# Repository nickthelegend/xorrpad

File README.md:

# xorrpad · v1.0.0

**Every market. One desk. Fourteen keys.**

xorrpad is a physical trading pad for Solana, backed by an Electron desk and
interfaces for the XOR phone app. Spot, perpetuals and YES/NO outcome markets
share programmable keys, an agent, remembered risk rules and an acceptance gate.
The ESP32-S3 prototype has 14 keys, a microphone, an amp and a 2.8-inch TFT.
The protocol supports a size/leverage knob; the current board has no wired encoder.

The order of work is a working board demo, then waitlist and reservations, then
bulk manufacturing. v1 uses your own local model or provider account and keys;
a paid hosted LLM service is outside this release. Nothing is removed in v1:
the original desk remains at `/classic`, alongside the nine-page desk, legacy
HTTP/voice paths, tokenized-stock book and NYSE-hours warnings.

## Architecture

```text
 ESP32-S3 pad                         XOR phone app (external Expo project)
 14 keys · mic · amp · TFT            BLE pairing/relay · signals · accept/deny
 link manager: USB > BLE > Wi-Fi <--> wallet signing · push integration target
       | USB-CDC NDJSON / Wi-Fi HTTPS             | HTTPS / wallet handoff
       v                                          v
 XOR desk (Electron on the Mac mini; responsive authenticated web view)
 ├─ serial / BLE central / HTTP / WebSocket link server and key programmer
 ├─ agent: Ollama locally or over Tailscale, or a bring-your-own-key provider
 ├─ voice: Deepgram STT → gated proposal → Deepgram TTS to desk / pad amp
 ├─ aggregator: Jupiter spot · Meteora DLMM · Phoenix perps · Jupiter Perps
 │              pm-AMM outcome markets on devnet
 ├─ memory + permissions → manual / policy auto-accept → executor
 │                         phone wallet (default) | capped session wallet
 └─ pad mirror · trade · predict · chats · models/keys · permissions
    positions · backtest · link; confirmed signature / Explorer receipt

 Separate devnet keeper: recurring pm-AMM markets + exact-expiry Pyth resolution
 Standalone site: waitlist + terms-gated Solana Pay USDC reservation checkout
```

The phone app source is not in this repository. Its BLE relay, notifications and
acceptance UI are integration targets, not a verified shipped phone release.
Transport tests prove the host simulator path. Firmware is **compiled, not yet
flashed**; physical BLE, keys, display, mic and amp still need a board check.
See [TESTING.md](TESTING.md) for the current full run and exact blockers.

## Venues

| Route / adapter id | Network | Implemented capability | Execution limit |
| --- | --- | --- | --- |
| Jupiter spot / `solana` (`jupiter` in router) | Mainnet reads | Mint-pinned spot/xStocks quotes and unsigned swaps; Jupiter can route through Meteora, Orca, Raydium and Phoenix spot | Live liquidity/quote required; a catalog entry does not guarantee a route |
| Meteora DLMM / `meteora` | Mainnet reads | Direct USDC-pair discovery, quotes and unsigned swaps, compared with Jupiter | No direct pool is reported as unlisted |
| Phoenix perps / `phoenix` | Mainnet reads | Live market discovery, depth quotes, position reads, unsigned open and ReduceOnly close | Enabled, funded trader/subaccount required; no public perps devnet verified |
| Jupiter Perps / `jupperps` | Mainnet reads | SOL/ETH/BTC marks, indicative quotes, on-chain fee reads, unsigned API open/close builders | Funded owner required; quote excludes ongoing borrow costs and is not a fill guarantee |
| PREDICT pm-AMM / `pmamm` | Devnet only in this app | Live YES/NO quotes, unsigned create/swap/claim, positions, creator-filtered stats and resolution evidence | Needs devnet SOL and mUSDC for a trade; funded end-to-end cycle remains blocked |

Every venue adapter only reads or builds unsigned transactions. The shared
executor handles signing/submission after acceptance. Missing fees remain unknown,
never zero. Token identity is the exact mint (or catalog `symbol@mint`), not a
ticker match; historical xStock liquidity exclusions are retained. Perp `size`
is USD collateral and notional is size × leverage; spot sells use asset units,
spot buys use USDC, and prediction sizes use devnet mUSDC.
[Venue evidence and quote assumptions](docs/VENUES.md).

## Trade lifecycle

1. **Signal:** a pad key, strategy scan, chat or voice intent creates a proposal.
2. **Proposal:** the aggregator compares real quotes and fees across eligible venues.
3. **Gate:** memory rules run before permissions: trade/day caps, leverage,
   position limits, venue/market allowlists, deny rules, cooldown and quiet hours.
4. **Accept or refuse:** press ✓/✗ on the pad or use the desk/phone integration.
   Waiting signals expire (60 seconds by default). Auto-accept is off by default;
   both venue and product kind must be enabled and the action logged and spoken.
   Unavailable speech leaves it awaiting manual acceptance.
5. **Sign:** the phone wallet is the default. Optionally create/fund a local
   session wallet and select session mode. The executor refreshes the quote and
   gate, reserves budget and checks the exact message again before signing.
6. **Execute and receipt:** after chain confirmation, persist the signature and
   Explorer link and publish them to the desk, TFT and connected event clients.
   An accepted proposal or unsigned handoff is never shown as a confirmed fill.

[Permissions, state transitions and wallet callbacks](docs/v1/T2-SIGNALS.md).

## Safety model

- The pad holds no wallet or model keys. The model can propose through tools;
  it has no tool to accept, sign, execute or change policy.
- Electron stores API credentials and session keys with OS-backed `safeStorage`
  (Keychain on macOS). Unavailable encryption fails closed. The optional Node
  session wallet uses an ignored owner-only 0600 file; it is not Keychain storage.
  Node refuses API-key persistence without Electron encryption.
- The local session signer checks RPC genesis and requires exactly
  `XORR_ALLOW_MAINNET=I_ACKNOWLEDGE_REAL_FUNDS` for mainnet. This switch does not
  configure or approve a phone wallet. Our transaction tests use devnet only.
- Permissions restrict memory decisions; deleting memory lowers fallback limits
  and removes knowledge of holdings. Corrupt policy fails closed. Ambiguous sends
  retain durable budget reservations and are not automatically retried.
- Hold KILL to disarm; pending unsigned signals are voided. A transaction already
  submitted cannot be cancelled. Keep authentication on all pad/phone relays and
  use a private, unique pad token before making the backend remotely reachable.
- pm-AMM resolution is creator-operated: the keeper records exact-expiry Pyth
  evidence but the program does not verify a Pyth proof. Confidence intervals
  touching a strike remain unresolved. Mainnet perps plus devnet predictions are
  research proposals, not an economic hedge.

## Setup

### Desk and memory

Use Node 20+ for desk/keeper (the site requires Node 22.12+ or 24+) and Python 3.
From the repository root:

```sh
python3 -m venv .venv
.venv/bin/pip install -r desk/memory/requirements.txt
npm ci --prefix desk
npm ci --prefix keeper
npm start --prefix desk
```

Electron starts the backend on port **8710** and opens setup. Enter the pad token
and provider/Deepgram keys in the desk's setup or **Models & keys**, then restart
when changing the pad token. Do not put secrets in source or plaintext files.
The browser desk uses the same backend; `/classic` preserves the original view.
For a headless backend, use `PORT=8710 HOST=127.0.0.1 node desk/main/server.mjs`
and supply configuration through your process environment. It does not offer
Electron credential persistence. Do not load `.env` files for tests.

### Pad: USB, BLE and Wi-Fi

Install Arduino CLI, the ESP32 core and libraries from
[firmware/README.md](firmware/README.md), then compile from the root:

```sh
arduino-cli compile --fqbn esp32:esp32:esp32s3:FlashSize=16M,PartitionScheme=app3M_fat9M_16MB,PSRAM=opi,CDCOnBoot=cdc firmware/xorrpad
```

This is a compile command, not a flash. The documented FQBN enables native CDC,
16 MB flash, the 3 MB app partition and OPI PSRAM for audio buffers.

- **USB:** connect the board's native USB-C. The desk scans Espressif serial
  devices at 115200; set `XORR_PAD_SERIAL` to select an explicit device path.
- **BLE:** the pad exposes Nordic UART; the desk's optional
  `@abandonware/noble` central or an external phone relay carries the same records.
  Enable Bluetooth access for the host. Physical radio/phone behavior is unverified.
- **Wi-Fi:** first boot/hold MIC at boot opens `xorr-pad-setup`. Join it, open
  `http://192.168.4.1` if needed, and enter Wi-Fi, `http://<mac-lan-ip>:8710`
  and the matching pad token. A reachable pinned-TLS HTTPS relay is also supported.
  The manager prefers responsive USB, then BLE, then Wi-Fi; uncertain trade
  inputs are not replayed after a transport change.

Use the desk **Pad** page to save/push the full 14-key map; MIC, KILL and
confirm/refuse cells stay protected. The **Link** page shows transport, version
and setup state. [Protocol](docs/v1/PAD-PROTOCOL.md) ·
[No-board simulator and real serial/PTY test](tools/padsim/README.md).

### Phone and Tailscale

Run the XOR Expo app from its separate project once Nick supplies its location
and build. Configure it to the desk HTTPS origin and matching pad token, pair the
pad's Nordic UART service, relay v1 records to authenticated `/padlink`, subscribe
to `/events`, and wire signal accept/refuse and wallet signing callbacks from
[T2](docs/v1/T2-SIGNALS.md). This is the integration contract; this repo has no
phone installation/build command or verified push-notification path.

Join the Mac mini, phone and any remote Ollama host to the same Tailscale network.
Use Serve for private HTTPS, or Funnel for a deliberately public HTTPS wallet/pad
relay, forwarding to port 8710 with backend authentication retained. A bare ESP32
**does not join Tailscale** and cannot route directly to a `100.x` tailnet IP;
use USB, LAN, a LAN relay or the pinned-TLS Funnel URL.

For wallet request URLs configure the relevant public HTTPS origin:
`SOLANA_PAY_PUBLIC_URL`, `PMAMM_PUBLIC_URL` and/or `PHOENIX_PUBLIC_URL`.
Set `SOLANA_ADDRESS` to the watched/phone wallet public key and
`PHOENIX_AUTHORITY` plus trader/subaccount indexes for Phoenix. A URL alone does
not prove a phone wallet signed and returned the correct message.

### Ollama, provider keys and voice

Start Ollama on the Mac mini or another reachable host and pull a tool-capable
model. In **Models & keys**, choose Ollama, set its root URL
(`http://localhost:11434` or your reachable Tailscale host), **Load models** and
select the installed model. Other choices are Anthropic or an OpenAI-compatible
provider with its API base URL and selected model. Enter keys in Electron's UI;
never include credentials in the provider URL. [Agent and chat guide](docs/v1/T3-AGENT-VOICE.md).

Enter a Deepgram key for Nova-3 STT and Aura TTS. Hold MIC to stream 16 kHz mono
PCM; enable desk playback with a user gesture. A missing key shows
`Setup required: DEEPGRAM_API_KEY`; no speech is synthesized locally to hide it.
Live model/voice verification and physical mic/amp verification remain separate.

### Keeper, backtest and landing

The optional keeper runs separately on devnet. Follow
[keeper/README.md](keeper/README.md): create its dedicated key once, fund with
at least 0.5 devnet SOL and the configured mUSDC liquidity budget, supply
`PYTH_API_KEY` in the process environment, then run `node keeper/run.mjs --cycle`
for a real create/resolve check. Never open its private key for documentation.

Backtest replays actual GeckoTerminal Solana pool candles, labelled with the
pool and DEX, with disclosed current fee schedules, funding gaps and adverse
slippage. Perps use the underlying spot reference plus the venue's live mark.
Pyth remains a secondary provider; its current HTTP 404 is reported when tried.
Partial archive coverage is explicit. Prediction replay is a counterfactual
curve experiment, not historical pm-AMM liquidity or proof of profitability.
[Replay contract and limits](docs/v1/BACKTEST.md).

```sh
npm ci --prefix site
npm run dev --prefix site
# http://127.0.0.1:8717
```

Waitlist storage requires Upstash; reservations need an approved price, merchant
and published terms. Missing setup leaves pre-orders disabled. The site verifies
finalized Solana Pay transfers; neither its API nor frontend signs payments.
[Site configuration and Vercel handoff](site/README.md).

## Deployment table

| Component | Local entry / target | Release state / exact handoff |
| --- | --- | --- |
| Desk | `npm start --prefix desk`; Mac mini, port 8710 | Source-run app; packaged app and public TLS/phone cycle need verification |
| Firmware | ESP32-S3 FQBN above | v1.0.0 compiled, not yet flashed; flash and sweep actual hardware |
| Phone | External XOR Expo app | Nick must supply repo/build and integrate relay, wallet and notifications |
| Keeper | `node keeper/run.mjs`; no listener | Fund dedicated devnet wallet and supply Hermes key before a real cycle |
| Landing | `site/`, port 8717; Vercel static + Node functions | Local build verified; configure Upstash/terms/merchant and deploy Preview, then Production |
| Remote access | Tailscale Serve/Funnel → desk 8710 | Configure HTTPS, token and wallet public URL; verify from the phone/pad |
| Models/voice | Ollama host or provider; Deepgram | Bring your own model/keys; paid hosted LLM deferred |

## Hackathon: Solana Perps & Prediction Markets

Target: [Perps and Prediction Markets](https://hackathons.solana.com/hackathons/perps-and-prediction-markets),
including Spark's **Best use of the pm-AMM by PREDICT** bounty. Its public listing
requires a working public repository and short demo, and weights real on-chain
traction most heavily. It lists a December 5, 2026 deadline; the bounty is a
$1,000 investment, with support to raise up to $25,000 on Backable.

pm-AMM is central to the Predict layer: quotes, YES/NO intent, creation, claims,
creator stats, keeper resolution and hedge proposals all use its actual markets.
Short-lived price-above-strike questions fit its expiry-aware outcome model.
A seeded AMM offers a quote without maintaining a two-sided order book;
parimutuel pools defer payout odds rather than provide the same continuous
entry/exit mechanism. Compared with LMSR or a generic constant-product pool,
the dynamic pm-AMM adjusts liquidity with time to expiry to target uniform
expected arbitrage loss under the paper's assumptions. This is a model property,
not guaranteed LP profit. [Protocol explanation](https://predict-pm-amm.dev/) ·
[Paradigm paper](https://www.paradigm.xyz/2024/11/pm-amm).

We do not claim borrowed reference transactions as users or revenue. Funded
keeper/trade cycles, independent users and a public demo must be demonstrated
before claiming bounty eligibility. The fact-filled draft and Nick-only TODOs
are in [HACKATHON_SUBMISSION_FORM.md](HACKATHON_SUBMISSION_FORM.md).

## Verification and layout

Run the complete discovered test set without parallel RPC bursts:

```sh
node --test --test-concurrency=1 desk/test/*.test.mjs keeper/test/*.test.mjs site/test/*.test.mjs
npm run test:ui --prefix desk
npm run test:ui --prefix site
npm run format:check --prefix site
npm run build --prefix site
make -C tools/uipreview shots
```

[TESTING.md](TESTING.md) gives one consolidated run, all skips, failures and
BLOCKED actions. Tests use real services and SQLite; no mocked quotes or receipts.

`firmware/xorrpad/` is the board sketch; `desk/main/` holds adapters, memory,
policy, agent and executor; `desk/renderer/` holds v1 and Classic; `keeper/` is
the separate oracle process; `site/` is the standalone landing; `tools/padsim/`
and `tools/uipreview/` verify host transport and display layout; `cad/` contains
the printable enclosure. [Spec](docs/v1/SPEC.md) · [Changelog](CHANGELOG.md).

MIT · Copyright (c) 2026 Nivesh Gajengi. No tag is created by T8; Claude tags
`v1.0.0` after review.

Art generated with ChatGPT; pad renders from the real CAD.
The [studio render pipeline](tools/render3d/README.md) and
[asset prompts/provenance](tools/render3d/ART-PROMPTS.md) document the source.

The finishing-pass [desktop contact sheet](docs/screens/v2/sheet-3d.jpg) records
all six screens at 1440 and 375 plus the command palette. The shared offline
studio rig, bounds-based framing and [timestamped SOL snapshot](desk/app/public/media/pad/SCREEN-SNAPSHOT.json)
keep the CAD renders and desktop consistent. `offline.png` is the explicit offline
asset; the hero and turntable show the firmware's real home screen. Teaser media
was copied in a separate local `xorrpad-teaser` commit; nothing was pushed.

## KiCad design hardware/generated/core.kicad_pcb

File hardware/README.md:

# xorrpad PCB: engineering draft — DO NOT ORDER

Created 2026-11-12 for the [business brief](../docs/business/BRIEF.md). **A human PCB designer must review and finish the schematic, placement and routing before any order.** No files were uploaded to a vendor, no orders placed and no hardware energized/flashed. Pro P1 and Core P2 now have locally routed boards with clean KiCad DRC; these remain engineering drafts, not production releases.

## P3 fabrication exports and fit result, 2026-11-12

**A human PCB designer must review this before any order.** P3 produced local review packages for [Core](generated/core/fab/) and [Pro](generated/pro/fab/), using **KiCad CLI 10.0.6** and the final P2/P1 boards. Both source PCBs are unchanged; each package's [Core manifest](generated/core/fab/manifest.json) / [Pro manifest](generated/pro/fab/manifest.json) records source/output SHA-256 hashes, commands in `export.log`, population, missing 3D models, and the fresh DRC result. No order, vendor upload, or push occurred. These exports are engineering review artifacts, not a manufacturing release.

| P3 result | Core | Pro |
| --- | ---: | ---: |
| DRC before P3: errors / warnings / unconnected | 0 / 0 / 0 | 0 / 0 / 0 |
| Fresh P3 DRC: errors / warnings / unconnected | **0 / 0 / 0** | **0 / 0 / 0** |
| Gerber layers / job file | 11 / 1 | 11 / 1 |
| Excellon drill files | PTH + NPTH | PTH + NPTH |
| Plated / non-plated drill features (including slots) | 346 / 44 | 365 / 45 |
| Regenerated JLC BOM groups / component references | 20 / 85 | 27 / 72 |
| Regenerated CPL references | 85 | 72 |
| Components with blank LCSC IDs | 8 | 16 |
| Native review schematic pages / verified connected pins | 12 / 251 | 11 / 266 |
| Board PDF layer pages | 8 | 8 |
| Actual CLI PCB render views | top, bottom, three-quarter | top, bottom, three-quarter |
| Component references missing 3D models | 32 | 20 |

Remaining DRC warnings: **none**; no P3 severity changes or exclusions. Raw reports: [Core](generated/core/fab/core-drc.json), [Pro](generated/pro/fab/pro-drc.json). The historical original unrouted totals were Core **658 violations + 195 unconnected**, Pro **569 + 206**; P3 starts from the already clean P2/P1 boards. DRC does not certify power, signal integrity, component selection, or fit.

Each package includes four copper layers in signal/GND/3V3/signal order, front/back mask, paste and silkscreen, Edge.Cuts, a Gerber job file, separate metric PTH/NPTH Excellon files, drill maps and a drill report. Gerbers/drills share KiCad's absolute origin. BOM/CPL are regenerated and reconciled against the final board pads, footprint identities and SKiDL parts manifest. CPL uses PCB **(100,184) mm** as its lower-left bounding origin, +Y upwards, `T`/`B`, and KiCad rotations; no assembler orientation corrections are claimed. Blank supplier IDs, unresolved **ILIM_VALUE_TBD**, draft J3 and sourcing holds make these unsuitable for procurement as-is.

There was no existing native schematic to plot. [export-fab.py](export-fab.py) reconstructs editable hierarchical KiCad review schematics from each saved SKiDL netlist using installed library symbols. U8 and Pro J3 retain the original passive terminal models. Named global nets join sheets; source-open pins stay open, with no added no-connect or power flags. **Actual `kicad-cli sch export netlist` round trips reproduce every source reference/pin/named-net connection exactly** (251 Core / 266 Pro connected pins), and final PCB pad nets match the source manifest. This is a connectivity review schematic, not a newly signed-off electrical design/ERC result. PDFs: [Core schematic](generated/core/fab/core-schematic.pdf), [Pro schematic](generated/pro/fab/pro-schematic.pdf), [Core board](generated/core/fab/core-board.pdf), [Pro board](generated/pro/fab/pro-board.pdf). Board PDFs show all four copper layers, both silkscreens and both fabrication layers with Edge.Cuts, at 1.6x, viewed from above; bottom pages are not mirrored. Every page and all six renders were visually inspected locally.

Actual `kicad-cli pcb render` images: Core [top](generated/core/fab/core-top.png), [bottom](generated/core/fab/core-bottom.png), [three-quarter](generated/core/fab/core-three-quarter.png); Pro [top](generated/pro/fab/pro-top.png), [bottom](generated/pro/fab/pro-bottom.png), [three-quarter](generated/pro/fab/pro-three-quarter.png). Missing-model references are enumerated in each manifest (including sockets, encoder, USB, some ICs and LEDs); these renders do not establish a complete populated enclosure fit.

[FIT.md](FIT.md) now covers both final boards against all four relevant `cad/` sources: nominal wall/skirt gaps **0.600/0.500 mm**, boss/tower gaps **0.8976/0.5976 mm**, all 14 key centres matching, **zero PCB mounting holes**, and **52.8 mm2 cage overlap** at the prototype seating Z. Pro's **24.5 mm** FPC contact span exceeds the existing pod opening's **16.1245 mm** bounding diagonal; a straight flat passage fails. That pod is designed for a different headered panel. Both SKUs need PCB support/Z design; Pro additionally needs a validated panel/FPC route. The mechanical check is explicitly **not an assembled-fit pass**.

Reproduce exports locally from the repository root (uses the installed KiCad libraries; no network):

```sh
/Applications/KiCad/KiCad.app/Contents/Frameworks/Python.framework/Versions/Current/bin/python3 hardware/export-fab.py --sku core
/Applications/KiCad/KiCad.app/Contents/Frameworks/Python.framework/Versions/Current/bin/python3 hardware/export-fab.py --sku pro
python3 hardware/verify.py
```

The existing offline suite passes **8 tests**. Source/output hashes, BOM/CPL reference coverage, round-trip schematic connectivity, PDF page counts, PNG integrity and the Gerber/drill inventories were also checked. Electrical, RF, USB, power, procurement, footprint and mechanical holds below remain. **A human PCB designer must review this before any order.**

## Core P2 routing result, 2026-11-12

**Core: 0 errors, 0 warnings, 0 unconnected** (latest placement baseline: 0 errors / 0 warnings / 197 unconnected; original baseline: 411 errors / 247 warnings / 195 unconnected). [Routed board](generated/core.kicad_pcb), [actual KiCad DRC](generated/core-p2-drc.json), [hashes and measurements](generated/core-p2-summary.json), [routing reproduction](ROUTING.md#core-p2-final-result--2026-11-12). Official Freerouting 2.5.0 JAR on local Java 25 completed in 73.013 s with network denied; its session was imported and finished locally. Four-layer signal/GND/3V3/signal stack, 0.15 mm minimum trace/space, 0.6/0.3 mm vias, filled ground pours and **154 added stitching vias**. CAD key centres, footprint population and pad nets are verified; no DRC severity or exclusion was changed. Core CPL and all LED bypass-pad distances are regenerated. The offline suite passes **8 tests** for both boards.

Remaining DRC warnings: **none**. [Top](generated/core/p2/core-top.png), [bottom](generated/core/p2/core-bottom.png) and [three-quarter](generated/core/p2/core-three-quarter.png) local KiCad renders are review aids; some footprints lack 3D models. USB uses the same nominal 90 Ω geometry as Pro, with measured A-contact paths 44.49 mm DP / 35.88 mm DN; uncoupled fanout/skew and the two-via buck switch node still require signal/power-layout review. DRC is not electrical or manufacturing sign-off. [FIT.md](FIT.md) records actual XY clearances and the existing cage interference; the populated PCB still needs a mounting/support/Z design. ILIM_VALUE_TBD and sourcing blockers remain. This P2 completed Core routing; the later P3 section above records fabrication review exports. Manufacturing release remains outstanding. Nothing was ordered, uploaded or pushed. **A human PCB designer must review this before any order.**

## Pro P1 routing result, 2026-11-12

**Pro: 0 errors, 0 warnings, 0 unconnected** (placement baseline: 0 errors / 207 unconnected). [Routed board](generated/pro.kicad_pcb), [actual KiCad DRC](generated/pro-p1-drc.json), [hashes and measurements](generated/pro-p1-summary.json), [routing provenance and reproduction](ROUTING.md). Official Freerouting JAR sessions were imported, then finished locally. Four-layer signal/GND/3V3/signal stack, 0.15 mm trace/space minima, 0.6/0.3 mm vias, filled GND pours and 166 added stitching vias. CAD key centres and DRC severities/exclusions are unchanged. Final Pro CPL and bypass distances are regenerated.

Remaining DRC warnings: **none**, so no waivers apply. USB has a nominal 90 Ω geometry target; impedance, uncoupled connector fanout, measured skew and the buck switch-node route require human review as detailed in ROUTING.md. FPC, input-limiter, sourcing and mechanical-fit production blockers below remain. Core routing and fabrication exports were outside this historical Pro P1 step; see P2 and P3 above. Manufacturing release remains outstanding. Nothing was ordered, uploaded or pushed. **A human PCB designer must review this before any order.**

## Files and reproducibility

- [circuit.py](circuit.py): SKiDL electrical source for Core and Pro, with explicit supplier MPNs/LCSC fields. [requirements.txt](requirements.txt) pins SKiDL 3.0.0. KiCad libraries provide actual electrical pin models; the FPC and proposed input limiter have explicit terminal models, so ERC cannot certify their functional behavior.
- [layout.py](layout.py): uses KiCad's `pcbnew` to create placement boards and Specctra DSNs. Physical key centers, centred MIC and knob follow [cad/partlib.py](../cad/partlib.py). Other dimensions/placements are **design assumptions**: the initial 84 mm square PCB and proposed holes/two-layer routing experiment. The final `layout-v2.py` boards use boss notches with **no PCB mounting holes**, four copper layers and rounded/relieved outlines; see P3 and FIT.md for actual fit limits. Board Z, supports and case production changes require mechanical review.
- [generated/](generated/): each SKU's KiCad `.net`, complete parts/pin manifest, placement `.kicad_pcb`, project settings, `.dsn`, JLC-format BOM/CPL and raw DRC report. `pro` has **72** electrically assembled components; `core` **85**, excluding mechanical mounting holes and final switch/cap/case kits. Counts are derived from the generated manifests, not factory measurements.
- [route.py](route.py), [routing-result.json](generated/routing-result.json) and SKU router logs: bounded **local** Freerouting attempt with analytics and HTTP API disabled. SHA-256 ties each recorded attempt to its DSN. Processes are terminated by their exact child PID if the router fails/hangs; no persistent server is started.
- [verify.py](verify.py): offline artifact and price reconciliation checks; it does **not** validate circuits, RF, layout safety or a real manufactured product.

Build from the repo root (requires Python, KiCad and its symbol/footprint libraries):

```sh
python3 -m venv hardware/.venv
hardware/.venv/bin/pip install -r hardware/requirements.txt
hardware/.venv/bin/python hardware/circuit.py --sku pro
hardware/.venv/bin/python hardware/circuit.py --sku core
# macOS KiCad Python; Linux may expose pcbnew through its system Python instead.
/Applications/KiCad/KiCad.app/Contents/Frameworks/Python.framework/Versions/Current/bin/python3 hardware/layout.py
python3 tools/business-bom.py
kicad-cli pcb drc --format json --severity-all --output hardware/generated/pro-drc.json hardware/generated/pro-placement.kicad_pcb
kicad-cli pcb drc --format json --severity-all --output hardware/generated/core-drc.json hardware/generated/core-placement.kicad_pcb
python3 hardware/route.py --router /path/to/local/freerouting-cli
python3 hardware/verify.py
```

Set `KICAD_SYMBOL_DIR` and `KICAD_FOOTPRINT_DIR` for non-default installations. Generators do not contact any external API. `business-bom.py` uses saved [price observations](../docs/business/price-sources.json), not live quotes. Install/download tools only from their official sources. Tested: **KiCad CLI 10.0.6**, its bundled Python/pcbnew, **SKiDL 3.0.0**, and the [Freerouting v2.5.0 macOS ARM64 CLI release](https://github.com/freerouting/freerouting/releases/tag/v2.5.0), downloaded 2026-11-12. The [official CLI reference](https://github.com/freerouting/freerouting/blob/v2.5.0/docs/command_line_arguments.md) documents `-da`, local DSN input and disabled API settings; no hosted autorouting used.

## Historical initial verification results, 2026-11-12

These are the original unrouted baseline reports; the current Pro P1 and Core P2 results above supersede both DRC columns. Original reports remain preserved for provenance.

| Check | Pro | Core |
| --- | ---: | ---: |
| SKiDL ERC | 0 errors, **105 warnings** | 0 errors, **64 warnings** |
| KiCad DRC violations, all severities | **569** | **658** |
| Additional unconnected items | **206** | **195** |
| Freerouting session created | **No** | **No** |

ERC warnings include undriven power inputs, deliberately unused MCU/interface pins, terminal-model limitations and an unterminated final LED output. No fake power flags were inserted to suppress those findings. KiCad reports include shorts, overlapping courtyards, clearances, drilled-hole and silkscreen issues. Raw reports preserve all findings and the default ignored-check list; no existing tests or DRC rules were relaxed. A CLI report command exiting zero means it **wrote a report**, not that DRC passed.

Freerouting loaded both real DSNs, then its native build threw **`com.oracle.svm.core.jdk.UnsupportedFeatureError: SerializationConstructorAccessor class not found … ComponentOutline`**. The wrapper stopped each failed child by PID; exit **143**, no `.ses` output. See [Pro log](generated/pro-router.log), [Core log](generated/core-router.log) and [result](generated/routing-result.json). **That historical native-runtime failure was superseded for Pro by the successful official JAR workflow above; Core is now routed through the successful P2 JAR workflow above.** A designer can retry the Java runtime release or another supported local version, then import a successful SES into KiCad and rerun DRC; no routed result is claimed here.

The standalone `python3 hardware/verify.py` run passed **8 tests, 0 failures, 0 skips**. They verify distinct socket/matrix cells, separate CC pull-downs and BTL connections, SKU population/FPC straps, BOM/CPL reference reconciliation, populated netlists, component quantity-tier arithmetic/provenance/unknowns, current local routing evidence and explicit non-clean DRC evidence. They do not call external APIs or use mock chain responses. The existing desk/firmware regression suite was not rerun because no application/firmware source changed.

## Electrical and sourcing decisions to review

1. **14 genuine Kailh CPG151101S11 sockets**, each with its own 1N4148W matrix diode. Columns pull up and selected rows sink; diode cathodes face row nets. Logical cells follow the existing [agents.h](../firmware/xorrpad/agents.h) map, including its historically unverified positions. Physical key order follows CAD. A new PCB still needs every key tested against its role; reused pin names do not establish physical proof. Encoder GPIO21/47/38 are a **new mapping proposal**, not implemented firmware support.
2. Keep ESP32-S3-WROOM-1-N16R8 and its native USB pins; leave GPIO35/36/37 unused for octal PSRAM. Pro P1 and Core P2 add the four-layer antenna keepout, GND reference/stitching and USB routing geometry; USB impedance, strap pins and RF/system integration still require independent review. Consult [Espressif datasheet](https://www.espressif.com/sites/default/files/documentation/esp32-s3-wroom-1_wroom-1u_datasheet_en.pdf), read 2026-11-12. The module is not the original DevKit: case supports and USB opening need rework.
3. TPS62160 buck is proposed instead of dissipating the full load in an LDO. Feedback 620 kΩ / 200 kΩ and a 0.8 V reference give a nominal **3.28 V**, a derived design setting, subject to resistor/reference tolerance. Inductor saturation, effective capacitance, hot loop, exposed-pad vias and thermal measurements need review. [TI data sheet](https://www.ti.com/lit/ds/symlink/tps62163.pdf), read 2026-11-12. Proposed TPS2553 input switch has **ILIM_VALUE_TBD**: the board must not be powered as-is. Add/validate advertised-current detection, limiter tolerance, inrush and suspend/brightness/audio controls before energizing. Separate CC resistors alone are not a power budget.
4. Pro FPC pins follow EastRising ER-TFT028-4 Rev2.1; interface-II SPI straps IM3..0 = 1110. Logic/VCI to 3.3 V; RD high; parallel/RGB inputs grounded; unused touch/SDO/TE open. The panel has four parallel backlight chips, so the draft uses separate 100 Ω anode resistors and a PWM cathode MOSFET. Current, brightness and thermal limits still require the actual supplied panel. [Manufacturer PDF via distributor](https://www.icbanq.com/icdownload/V2_DATA/ICBShop/Board/DFDSAFJLSDA.pdf), read 2026-11-12.
5. **FPC footprint is a placement placeholder**, named `ER-CON50HT-1_DRAFT`: only its 50 positions / 0.5 mm pitch are sourced. Pad width/length and missing shell anchors are explicitly assumptions in `layout.py`. Replace it with a measured/manufacturer-verified top-contact land pattern, latch clearance and strain relief before manufacture. It is not JLC placement-approved.
6. Pro's ICS-43434 is a costed **NRND/EOL candidate**, not an approved production mic. Qualify a current I2S part; verify sample bit alignment and bottom acoustic port, gasket and sealing. MAX98357A/speaker are BTL; have the vendor crimp the PH harness and limit power to the selected speaker rating. Core omits audio and TFT; it needs a SKU-aware factory report and host prompts, not falsified passes for absent hardware.
7. Core uses 14 key LEDs plus status; base Pro status only. Both need LED voltage/pinout, bypass and brightness validation. Pro's optional key-RGB upgrade is a future population/layout change, not present in this draft.

## Formats, licensing and order gate

JLC BOM columns: `Comment,Designator,Footprint,LCSC Part #`. CPL columns: `Designator,Mid X,Mid Y,Layer,Rotation`, millimetres, proposed bottom-left board origin, positive Y upward. Bottom socket placements are marked `B`; no panel transforms, fixture tooling or JLC rotation corrections were applied. THT encoder/header must be purchased/soldered by the assembler. Blank LCSC fields and a syntactically valid CSV **do not mean JLC-ready procurement**. See [JLC BOM guidance](https://jlcpcb.com/help/article/bill-of-materials-for-pcb-assembly) and [CPL guidance](https://jlcpcb.com/help/article/pick-place-file-for-pcb-assembly), read 2026-11-12; final BOM/CPL needs the assembler's reviewed orientation/parts approval.

The socket compatibility footprint was fetched from [Keebio](https://github.com/keebio/Keebio-Parts.pretty/blob/master/Kailh_MX_Socket-compat.kicad_mod), read 2026-11-12. Its MIT license is preserved in [KEEBIO-LICENSE](KEEBIO-LICENSE). It contains compatibility through-holes/unused LED pads and routing cutouts: inspect against the actual Kailh drawing and decide a dedicated socket-only land pattern; do not blindly manufacture this community footprint. Other footprints/symbols are from the installed KiCad libraries; no vendor model uploaded.

Expected **review/re-layout budget scenario**: [Upwork](https://www.upwork.com/hire/pcb-designers/) publishes **$25–$50/hour**, read 2026-11-12. **ASSUMPTION:** 20–40 hours ⇒ **$500–$2,000**, excluding platform fees, prototypes and compliance; this can become a larger redesign. **Quote needed from the selected designer**. Required deliverables: checked schematic/ERC dispositions, actual pin/footprint drawings, power/RF/USB review, finished layout with clean/reasoned DRC, CAD interference checks, validated fabrication/assembly outputs and independent production-release sign-off. P3 includes local Gerber and drill review exports; no manufacturing/order release is included.

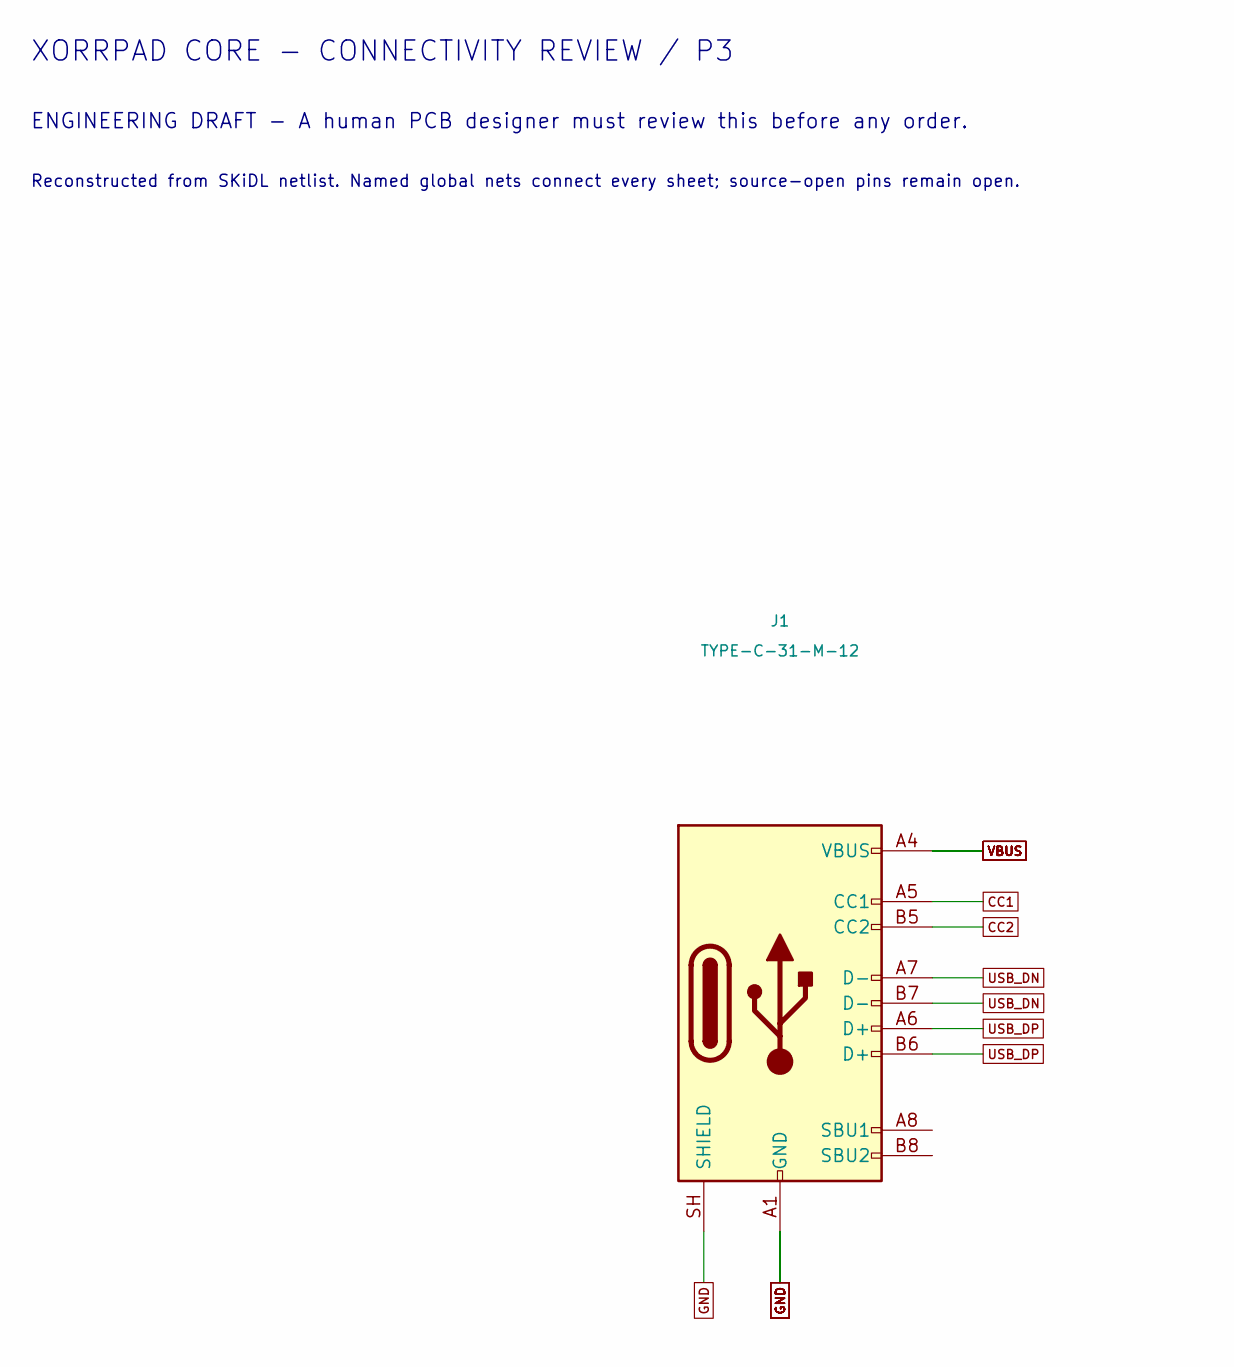
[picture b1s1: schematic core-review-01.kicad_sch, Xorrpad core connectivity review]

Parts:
J1: TYPE-C-31-M-12; USB_C_Receptacle_HRO_TYPE-C-31-M-12

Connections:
CC1: J1.A5 (CC1); also elsewhere on the board
CC2: J1.B5 (CC2); also elsewhere on the board
GND: J1.A1 (GND), J1.A12 (GND), J1.B1 (GND), J1.B12 (GND), J1.SH (SHIELD); also elsewhere on the board
USB_DN: J1.A7 (D-), J1.B7 (D-); also elsewhere on the board
USB_DP: J1.A6 (D+), J1.B6 (D+); also elsewhere on the board
VBUS: J1.A4 (VBUS), J1.A9 (VBUS), J1.B4 (VBUS), J1.B9 (VBUS); also elsewhere on the board

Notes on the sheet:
XORRPAD CORE - CONNECTIVITY REVIEW / P3
ENGINEERING DRAFT - A human PCB designer must review this before any order.
Reconstructed from SKiDL netlist. Named global nets connect every sheet; source-open pins remain open.

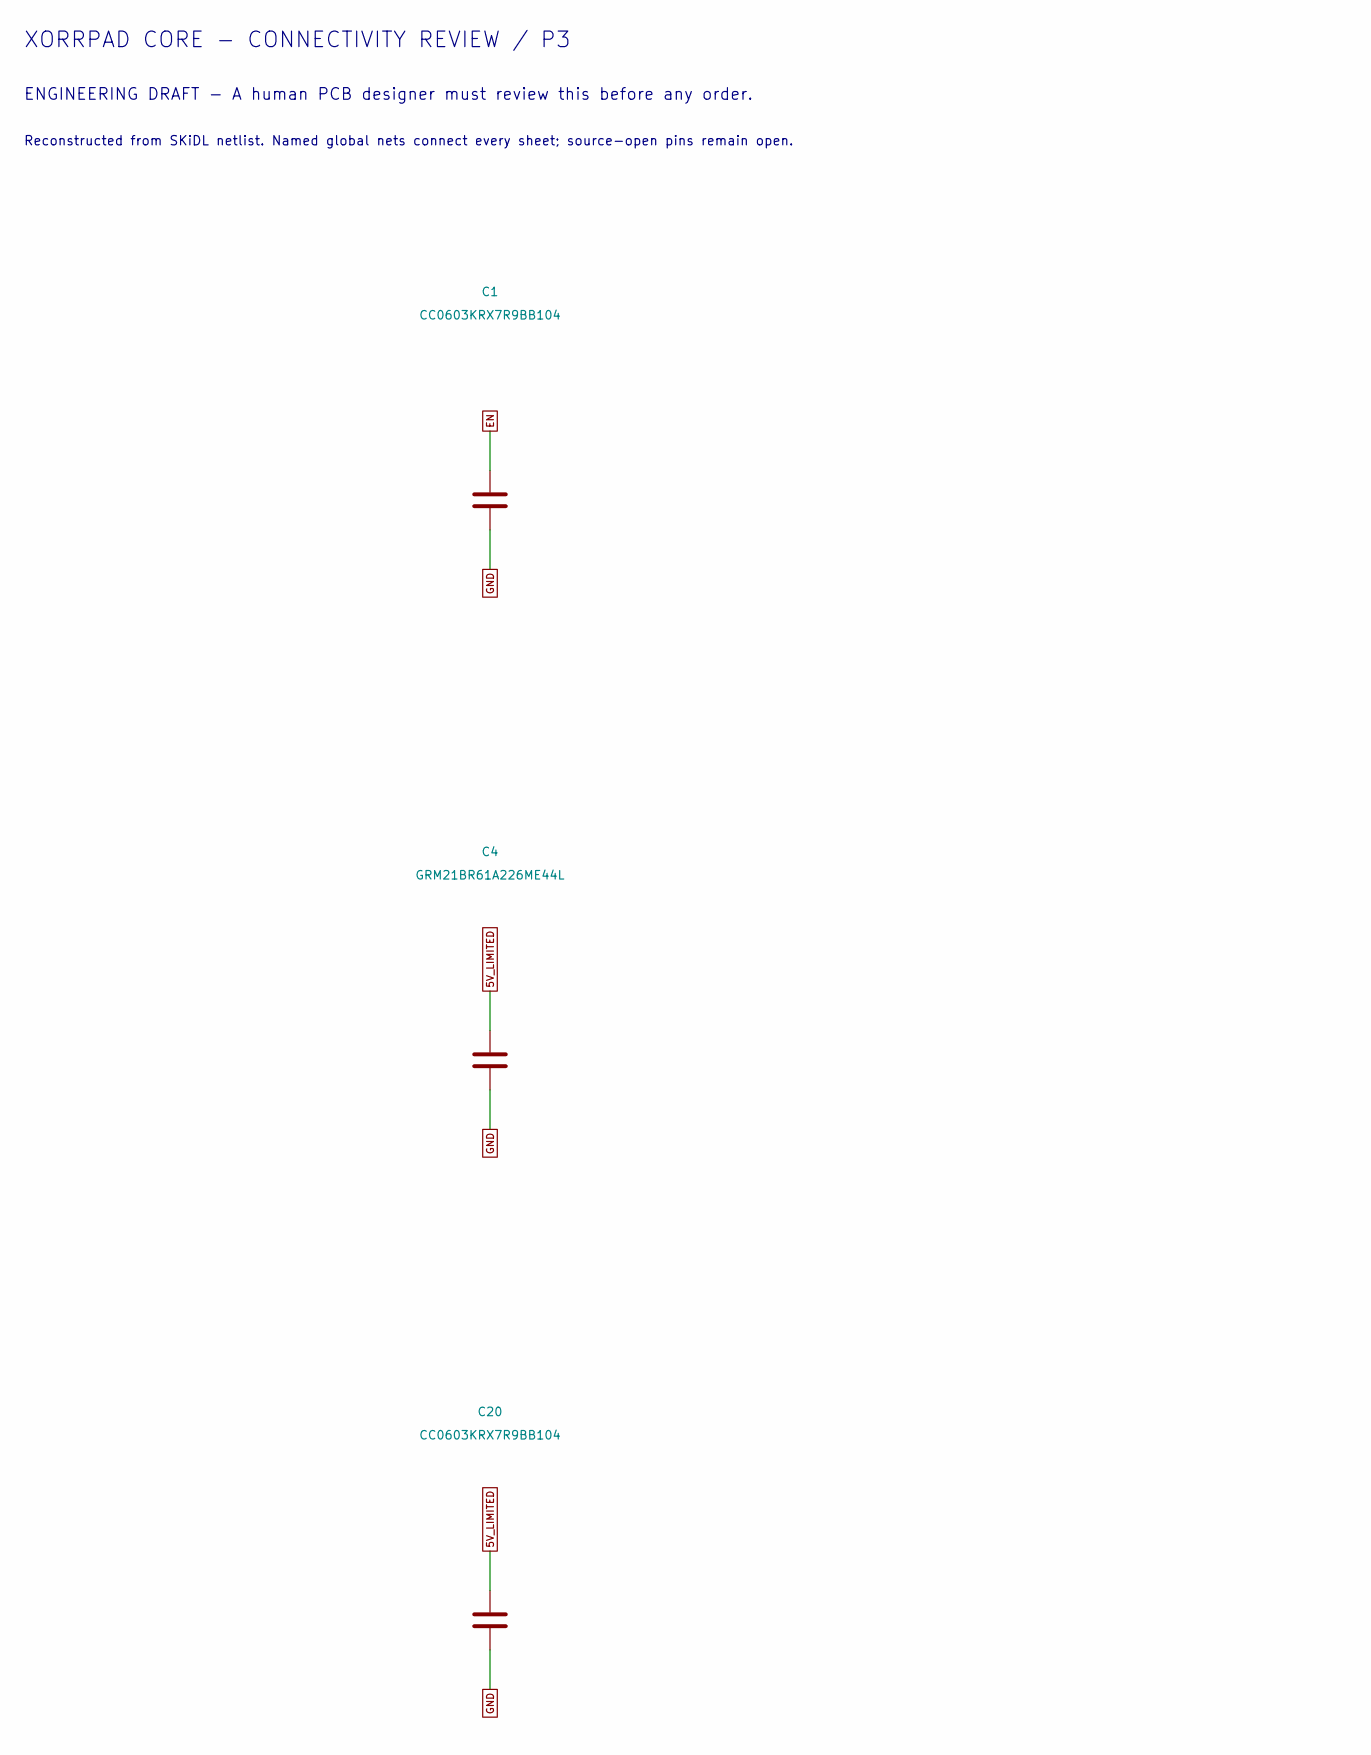
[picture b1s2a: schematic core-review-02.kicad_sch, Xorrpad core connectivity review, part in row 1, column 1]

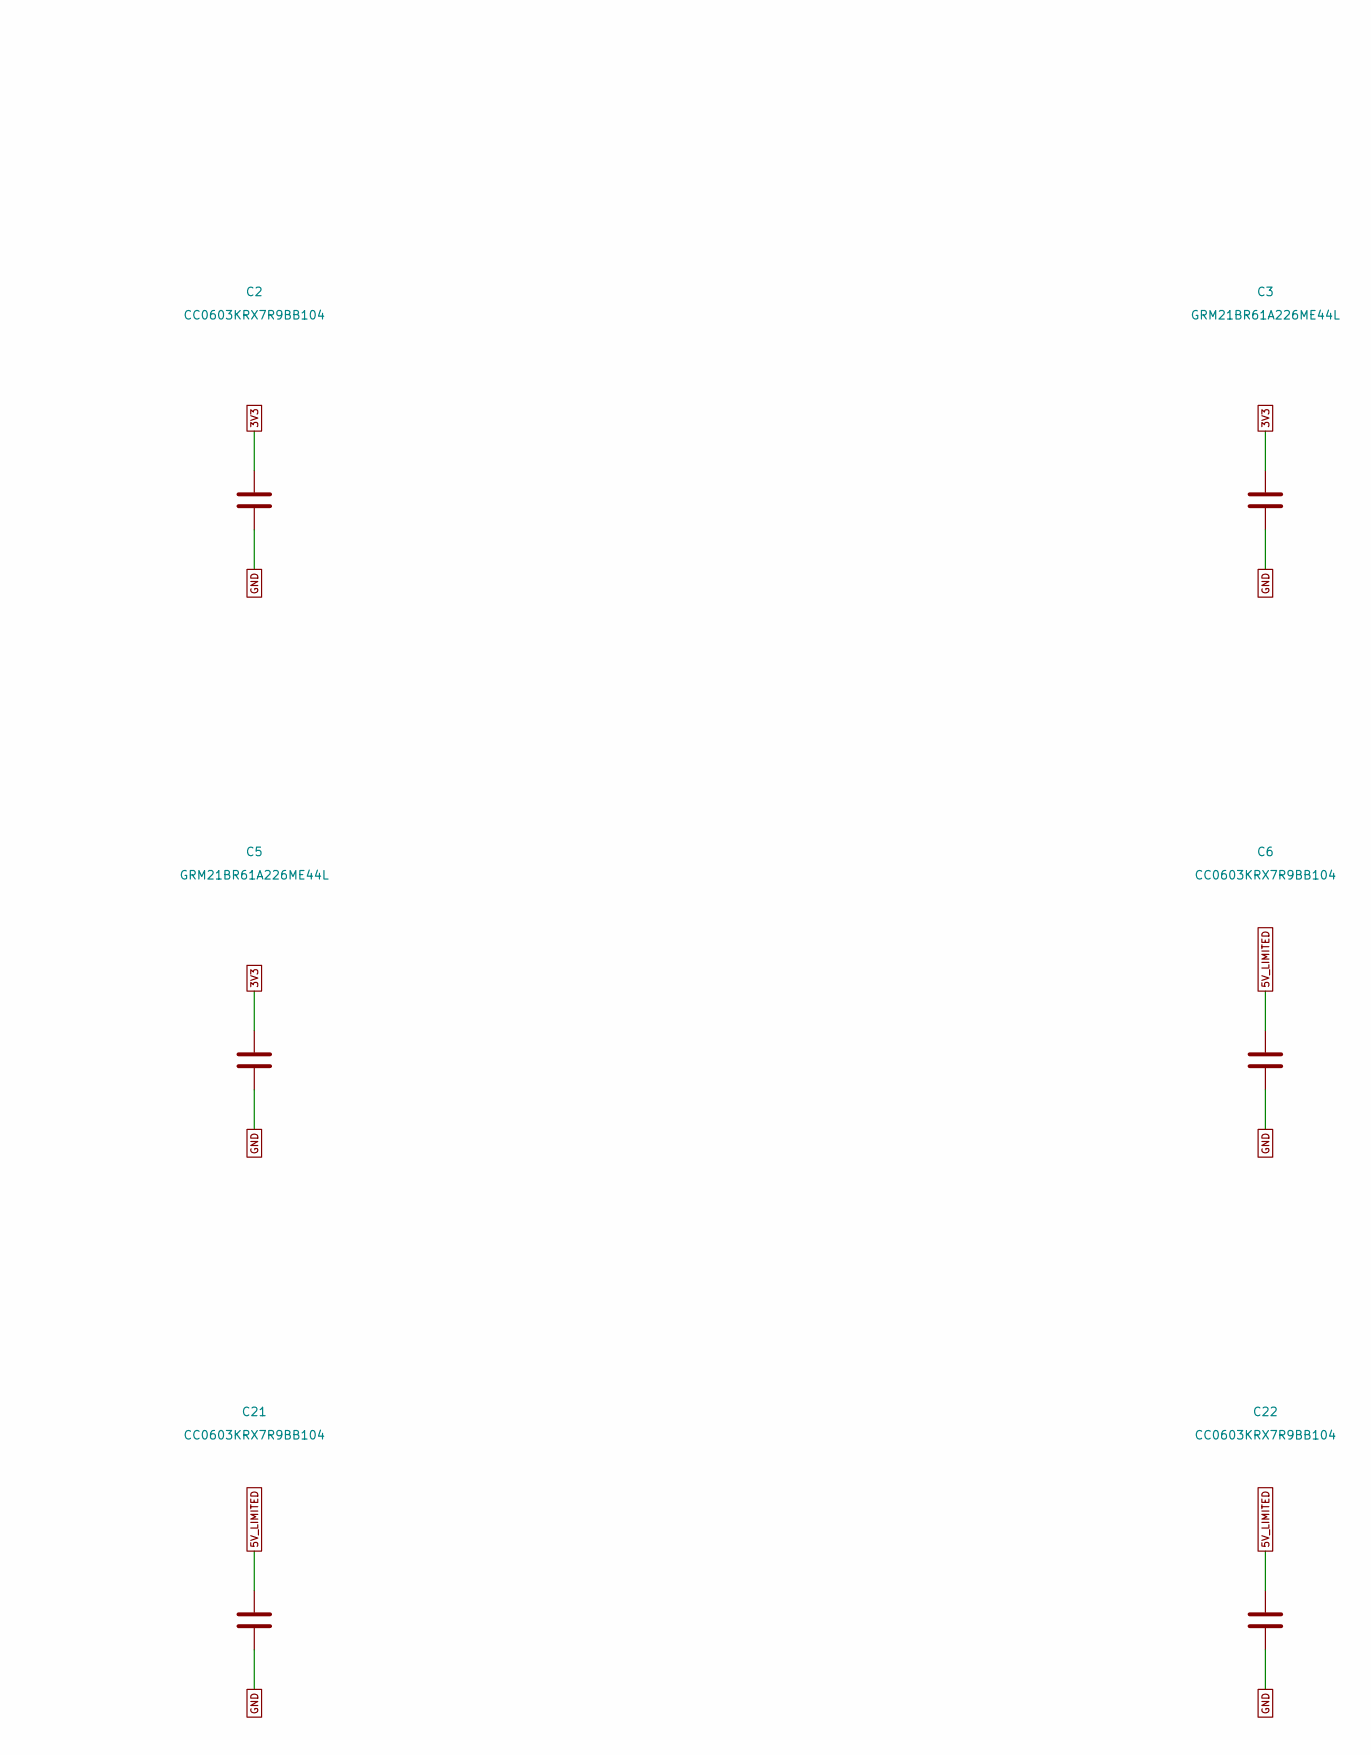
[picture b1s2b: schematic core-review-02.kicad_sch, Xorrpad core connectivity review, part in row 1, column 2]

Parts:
C1, C2, C6, C20, C21, C22: CC0603KRX7R9BB104; C_0603_1608Metric
C3, C4, C5: GRM21BR61A226ME44L; C_0805_2012Metric

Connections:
3V3: C2.1, C3.1, C5.1; also elsewhere on the board
5V_LIMITED: C4.1, C6.1, C20.1, C21.1, C22.1; also elsewhere on the board
EN: C1.1; also elsewhere on the board
GND: C1.2, C2.2, C3.2, C4.2, C5.2, C6.2, C20.2, C21.2, C22.2; also elsewhere on the board

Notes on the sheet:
XORRPAD CORE - CONNECTIVITY REVIEW / P3
ENGINEERING DRAFT - A human PCB designer must review this before any order.
Reconstructed from SKiDL netlist. Named global nets connect every sheet; source-open pins remain open.

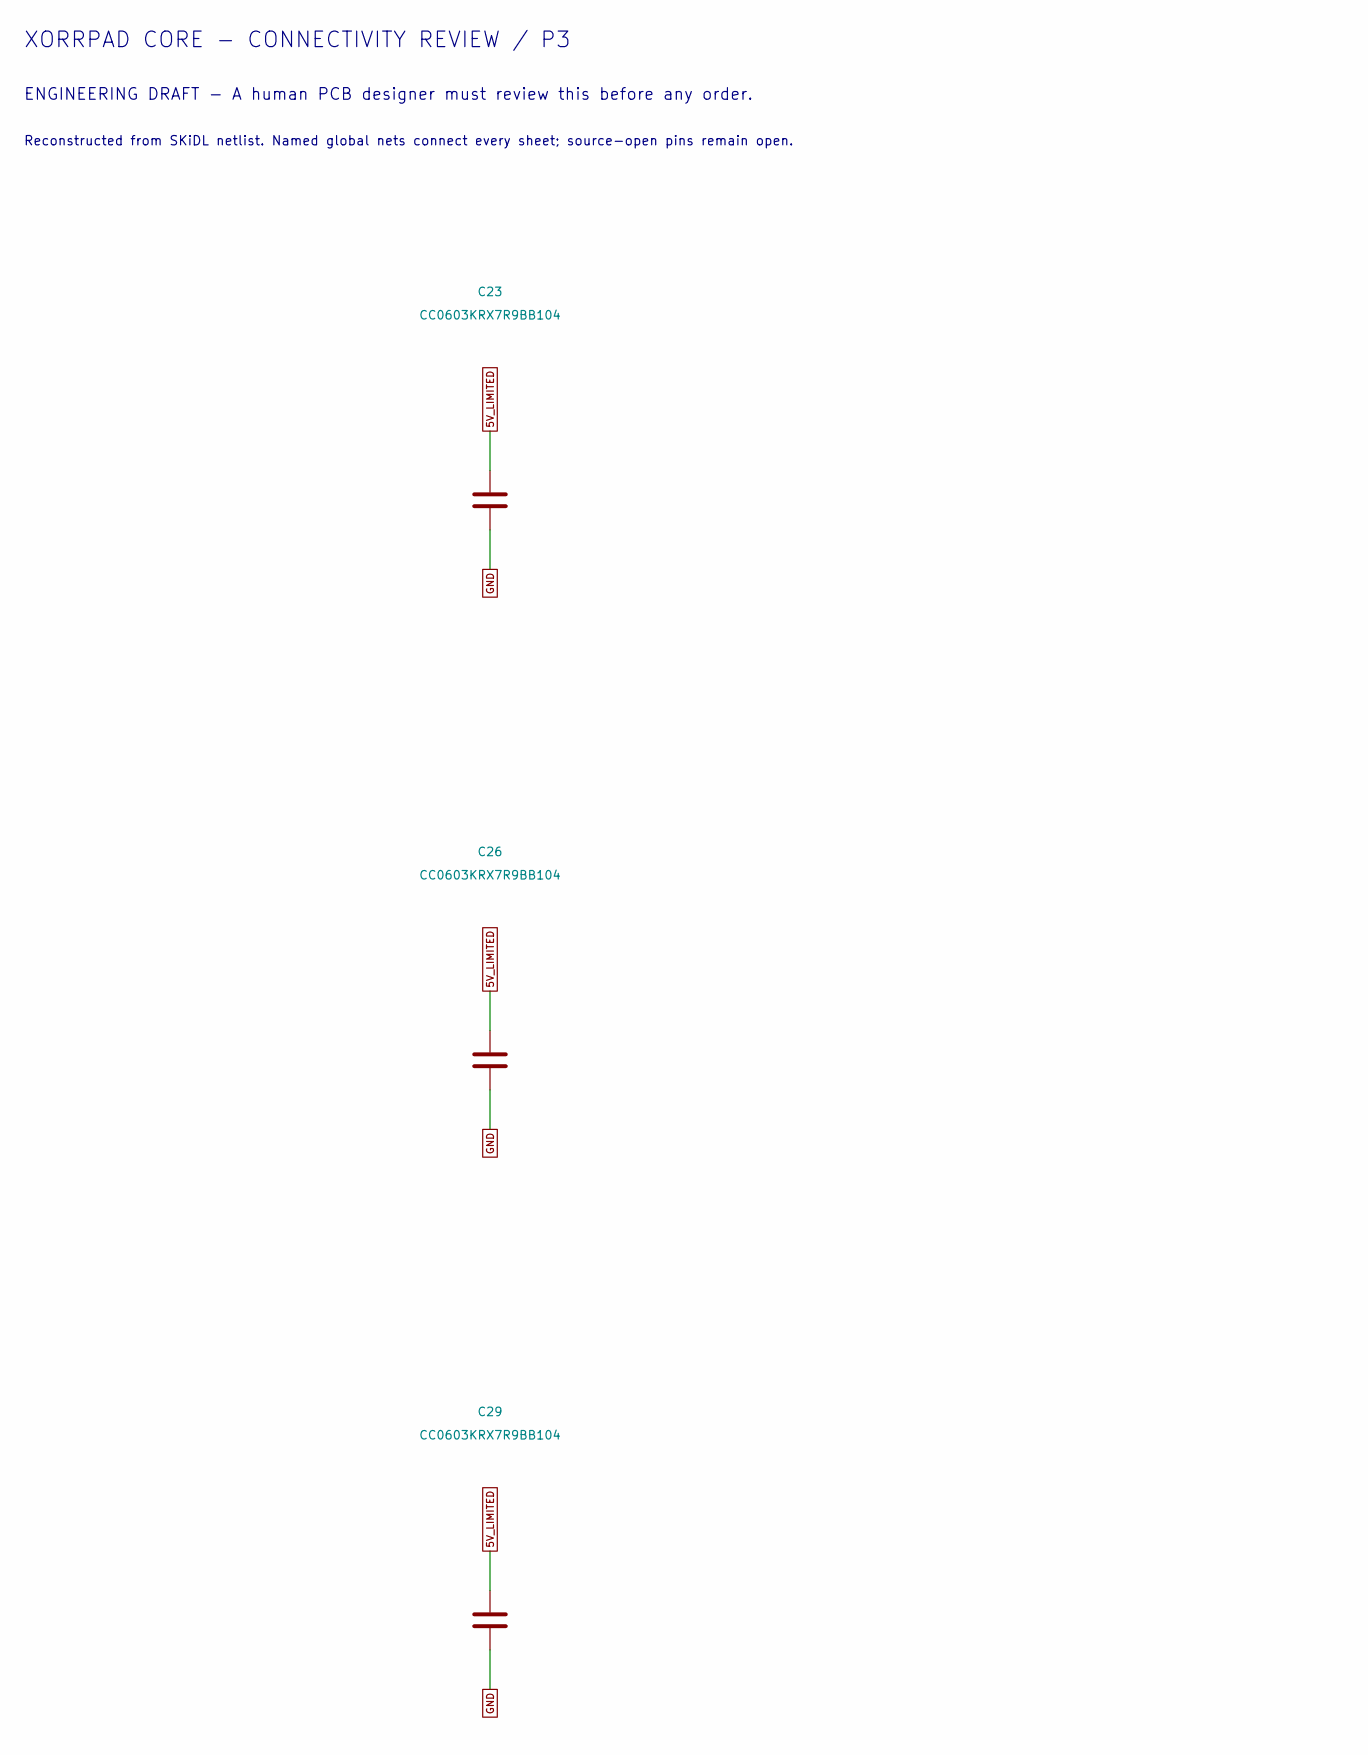
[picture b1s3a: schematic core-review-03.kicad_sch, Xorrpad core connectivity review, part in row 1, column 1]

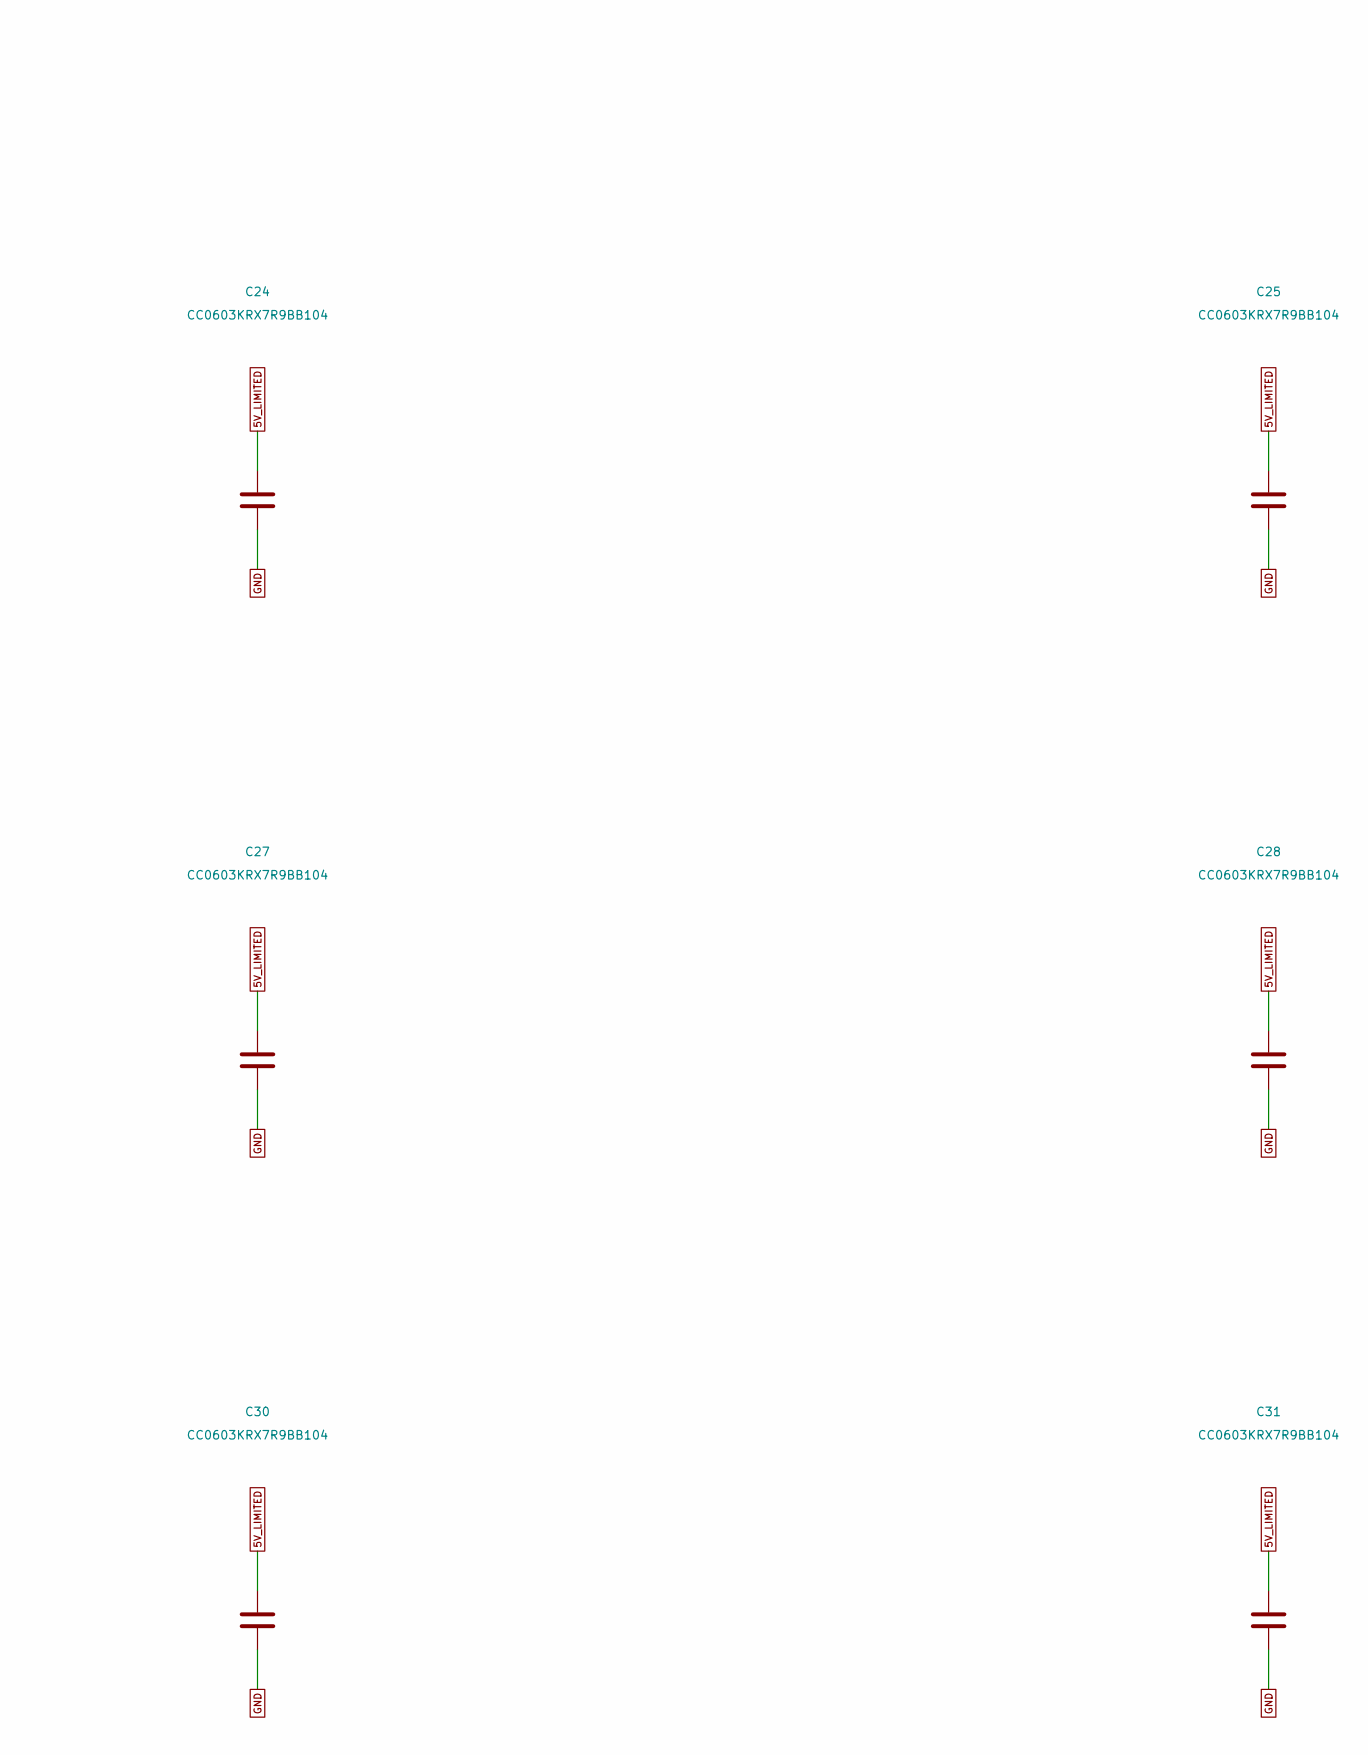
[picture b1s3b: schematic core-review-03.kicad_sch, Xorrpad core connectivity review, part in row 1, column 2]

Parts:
C23, C24, C25, C26, C27, C28, C29, C30, C31: CC0603KRX7R9BB104; C_0603_1608Metric

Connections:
5V_LIMITED: C23.1, C24.1, C25.1, C26.1, C27.1, C28.1, C29.1, C30.1, C31.1; also elsewhere on the board
GND: C23.2, C24.2, C25.2, C26.2, C27.2, C28.2, C29.2, C30.2, C31.2; also elsewhere on the board

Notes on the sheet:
XORRPAD CORE - CONNECTIVITY REVIEW / P3
ENGINEERING DRAFT - A human PCB designer must review this before any order.
Reconstructed from SKiDL netlist. Named global nets connect every sheet; source-open pins remain open.
